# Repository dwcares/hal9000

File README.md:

# HAL9000 Voice Assistant

A voice assistant powered by OpenAI running on Particle microcontrollers. Press a button to talk, receive AI-generated spoken responses. Designed to fit inside the [Moebius Models 1:1 HAL9000 kit](https://www.amazon.com/Moebius-Models-HAL9000-Styrene-MOE20015/dp/B07SVCLLFW).

> "I'm sorry Dave, I'm afraid I can't do that."

## Overview

HAL9000 demonstrates bidirectional audio streaming between a Particle device (Photon/Argon) and a Node.js server. The server uses OpenAI's Whisper for speech-to-text, GPT for conversation, and TTS for speech synthesis.

## Hardware

A custom carrier PCB is available for clean assembly. See the [hardware folder](hardware/) for KiCad source files and manufacturing outputs.

### Components

| Component | Description | Connection |
|-----------|-------------|------------|
| Particle Photon | Wi-Fi MCU | Socket headers |
| MAX9814 Mic Module | Electret mic with AGC amp | J_MIC1 (3.3V/MIC/GND) |
| PAM8302A Amp Module | 2.5W Class-D mono amp | J_AMP1 (5V/AMP/GND) |
| 6mm Tactile Button | Push-to-talk | SW1 |
| 5mm LED | Status indicator | J_LED1 |
| Battery + Switch | Power input | J_BATT1, J_SW1 |
| Buck/Boost Converter | 5V regulated supply | J_BUCK1 |

### Quick Wiring (without PCB)

```
Particle Photon
┌─────────────────┐
│              A6 │──── Mic OUT (MAX9814)
│              A3 │──── Amp IN (PAM8302A)
│              D4 │──── Button ────┐
│             GND │────────────────┴── GND
│            3.3V │──── Mic VCC
│              5V │──── Amp VCC
│              D0 │──── LED+
└─────────────────┘
```

## Setup

### 1. Server Setup

```bash
cd server
npm install
```

Create a `.env` file:

```bash
cp .env.example .env
```

Edit `.env` with your credentials:

```
OPENAI_API_KEY=sk-your-key-here
PARTICLE_USERNAME=your-email@example.com
PARTICLE_PASSWORD=your-password
```

Start the server:

```bash
npm start
```

The server will:
- Login to Particle Cloud
- Publish its IP address for device discovery
- Listen for incoming device connections

### 2. Firmware Setup

Install the Particle CLI if you haven't:

```bash
npm install -g particle-cli
particle login
```

Install dependencies and flash:

```bash
cd firmware
particle library install
```

Compile and flash:

```bash
particle compile photon . --saveTo hal9000.bin
particle flash YOUR_DEVICE_NAME hal9000.bin
```

Or use Particle Workbench in VS Code.

> **Note:** No need to configure server IP - the device discovers it automatically via Particle Cloud!

## Usage

1. Power on the Particle device
2. Wait for the LED to indicate connection (solid on)
3. Press and hold the button to speak
4. Release the button when done
5. Wait for HAL's response through the speaker

## Configuration

### Server Options

| Environment Variable | Default | Description |
|---------------------|---------|-------------|
| `OPENAI_API_KEY` | - | Your OpenAI API key (required) |
| `PARTICLE_USERNAME` | - | Particle account email (for cloud discovery) |
| `PARTICLE_PASSWORD` | - | Particle account password |
| `PORT` | `5000` | Server port |
| `OPENAI_MODEL` | `gpt-4o` | Chat model |
| `OPENAI_VOICE` | `alloy` | TTS voice (alloy, echo, fable, onyx, nova, shimmer) |
| `SYSTEM_PROMPT` | (default) | AI personality prompt |
| `SAVE_RECORDINGS` | `false` | Save audio recordings to disk |

### Firmware Options

Edit the defines at the top of `hal9000.ino`:

```cpp
#define MIC_PIN      A6       // Microphone input
#define SPEAKER_PIN  A3       // Speaker output (DAC)
#define BUTTON_PIN   D4       // Push-to-talk button
#define LED_PIN      D0       // Status LED
#define SERVER_PORT  5000
```

## How Discovery Works

The server and device find each other automatically via Particle Cloud:

```
┌─────────────────┐                      ┌─────────────────┐
│  Node.js Server │                      │  Particle       │
│                 │                      │  Device         │
│ 1. Login to     │                      │                 │
│    Particle     │                      │ 3. Subscribe to │
│    Cloud        │                      │    server-ip    │
│                 │                      │    events       │
│ 2. Publish      │─── server-ip ───────►│                 │
│    server IP    │    (via cloud)       │ 4. Cache IP in  │
│                 │                      │    EEPROM       │
│ 5. Listen for   │◄── device-online ────│                 │
│    device-online│    (via cloud)       │ 5. Connect via  │
│    (republish)  │                      │    TCP          │
└─────────────────┘                      └─────────────────┘
```

- **First boot:** Device waits for server IP via cloud event
- **Subsequent boots:** Device uses cached IP for instant connect
- **Server restart:** Publishes new IP, devices update cache

## Dependencies

### Server
- [microstream-server](https://www.npmjs.com/package/microstream-server) - Audio streaming
- [particle-api-js](https://www.npmjs.com/package/particle-api-js) - Cloud discovery
- [openai](https://www.npmjs.com/package/openai) - AI services
- [dotenv](https://www.npmjs.com/package/dotenv) - Environment config

### Firmware
- [microstream](https://build.particle.io/libs/microstream) - Audio streaming library

## Troubleshooting

### No audio heard from speaker
- Check speaker wiring to DAC pin (A3 on Photon)
- Verify amplifier has power
- Check server console for "Playing response..." messages

### "Disconnected" status
- Verify server is running and reachable
- Check firewall allows port 5000
- Confirm device is on same network

### Transcription errors
- Speak clearly and close to microphone
- Check microphone wiring and amplifier gain
- Try adjusting `sampleRate` if audio quality is poor

## Architecture

```
┌─────────────────┐     TCP/WS      ┌─────────────────┐
│  Particle       │◄───────────────►│  Node.js        │
│  (microstream)  │                 │  (microstream-  │
│                 │                 │   server)       │
│  - Mic capture  │                 │                 │
│  - DAC playback │                 │  ┌───────────┐  │
│  - Button input │                 │  │ OpenAI    │  │
└─────────────────┘                 │  │ - Whisper │  │
                                    │  │ - GPT-4   │  │
                                    │  │ - TTS     │  │
                                    │  └───────────┘  │
                                    └─────────────────┘
```

## License

MIT License - see [LICENSE](LICENSE)

## Credits

Built with:
- [Microstream](https://github.com/dwcares/microstream) - Bidirectional audio streaming
- [OpenAI](https://openai.com) - AI services
- [Particle](https://particle.io) - IoT platform

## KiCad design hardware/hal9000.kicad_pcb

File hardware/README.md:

# HAL9000 Hardware

Custom carrier PCB for the HAL9000 voice assistant, designed in KiCad. This board is sized to mount inside the [Moebius Models 1:1 scale HAL9000 kit](https://www.amazon.com/Moebius-Models-HAL9000-Styrene-MOE20015/dp/B07SVCLLFW).

## Overview

This PCB provides a clean way to connect a Particle Photon to all the peripherals needed for the voice assistant:
- Microphone input with filtering
- Amplifier output for speaker
- Push-to-talk button
- Status LED
- Battery power with switch

## Files

| File | Description |
|------|-------------|
| `hal9000.kicad_pro` | KiCad project file |
| `hal9000.kicad_sch` | Schematic |
| `hal9000.kicad_pcb` | PCB layout |
| `hal9000_bom.csv` | Bill of materials |
| `manufacturing/` | Gerber files for fabrication |

## Bill of Materials

| Reference | Qty | Description | Notes |
|-----------|-----|-------------|-------|
| U1 | 1 | Particle Photon | Main MCU |
| J_PHOTON_L1, J_PHOTON_R1 | 2 | 12-pin Female Header 2.54mm | Photon sockets |
| J_BATT1 | 1 | 2-pin Header | Battery input (VBAT+, GND) |
| J_SW1 | 1 | 2-pin Header | Power switch |
| J_BUCK1 | 1 | 3-pin Header | Buck converter (VBAT+, GND, +5V) |
| J_MIC1 | 1 | 3-pin Header | Mic module (+3V3, MIC, GND) |
| J_AMP1 | 1 | 3-pin Header | Amp module (+5V, AMP, GND) |
| J_LED1 | 1 | 2-pin Header | LED (GND, LED+) |
| SW1 | 1 | 6mm Tactile Button | Push-to-talk |
| R1 | 1 | 220Ω 0805 | LED current limiter |
| R2 | 1 | 1kΩ 0805 | Mic input filter |
| C1 | 1 | 10nF 0805 | Mic input filter |
| C2 | 1 | 470µF Electrolytic | 5V bulk capacitance |

## External Modules

These modules connect via headers:

| Module | Description | Header |
|--------|-------------|--------|
| MAX9814 | Electret mic with AGC amplifier | J_MIC1 |
| PAM8302A | 2.5W Class-D mono amplifier | J_AMP1 |
| Buck/Boost Converter | 5V regulated output | J_BUCK1 |

## Pin Mapping

| Signal | Photon Pin | Description |
|--------|------------|-------------|
| MIC | A6 | Microphone analog input |
| AMP | A3 (DAC) | Speaker DAC output |
| BUTTON | D4 | Push-to-talk input |
| LED | D0 | Status LED output |

## Power

The board supports battery power with an external switch:

```
Battery ──► J_BATT1 ──► J_SW1 (switch) ──► Buck Converter ──► J_BUCK1 (+5V out)
                                                                    │
                                                              Photon VIN
                                                                    │
                                                              Onboard 3.3V reg
```

- **5V rail**: Powers Photon (via VIN), amplifier module
- **3.3V rail**: Powers microphone module (from Photon regulator)

## Manufacturing

The `manufacturing/` folder contains Gerber files ready for PCB fabrication. Upload to your preferred PCB manufacturer (JLCPCB, PCBWay, OSH Park, etc.).

## Assembly Tips

1. Solder SMD components first (R1, R2, C1)
2. Install female headers for Photon (J_PHOTON_L1, J_PHOTON_R1)
3. Install remaining through-hole headers and button
4. Add electrolytic capacitor C2 (observe polarity)
5. Connect external modules via headers
6. Insert Particle Photon

## License

MIT License - see [LICENSE](../LICENSE)

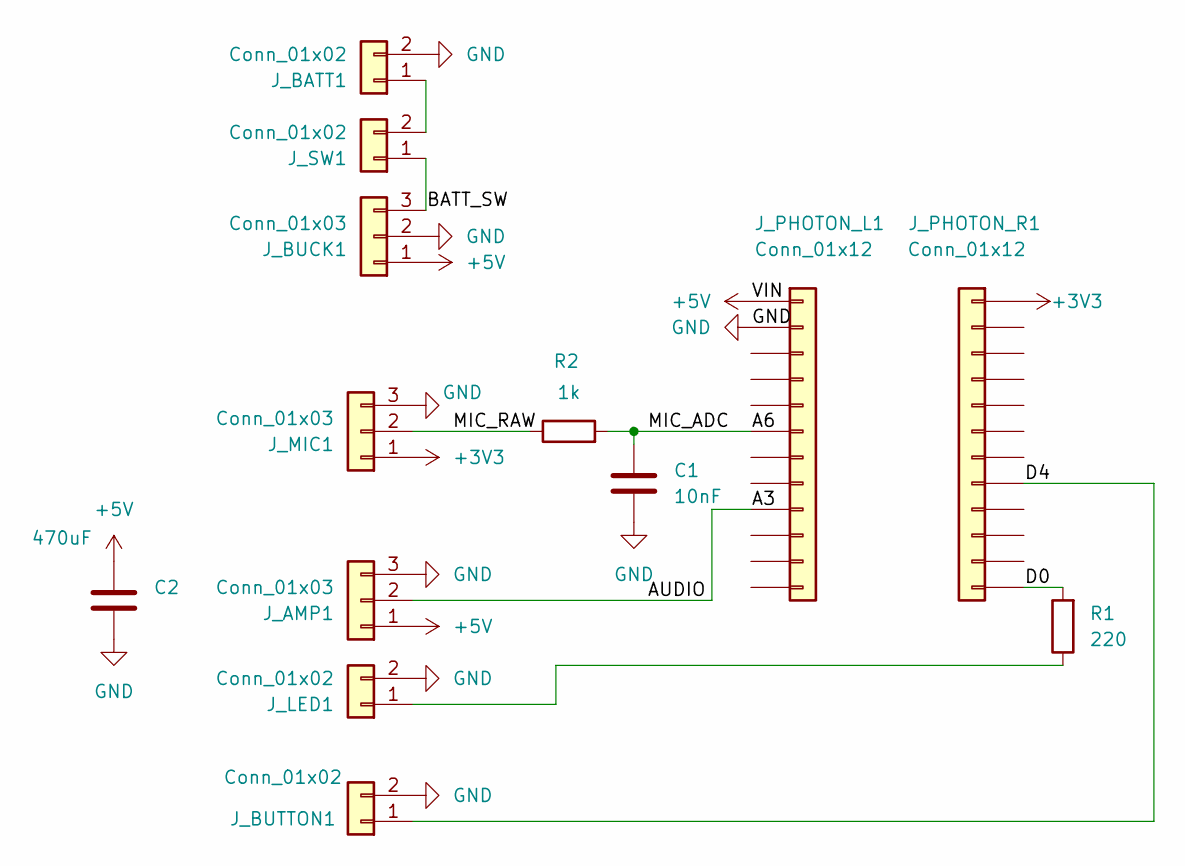
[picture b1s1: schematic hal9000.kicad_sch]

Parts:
C1: 10nF; C_0805_2012Metric_Pad1.18x1.45mm_HandSolder
C2: 470uF; CP_Radial_D6.3mm_P2.50mm
J_AMP1: Conn_01x03; PinHeader_1x03_P2.54mm_Vertical
J_BATT1: Conn_01x02; PinHeader_1x02_P2.54mm_Vertical
J_BUCK1: Conn_01x03; PinHeader_1x03_P2.54mm_Vertical
J_BUTTON1: Conn_01x02; PinHeader_1x02_P2.54mm_Vertical
J_LED1: Conn_01x02; PinHeader_1x02_P2.54mm_Vertical
J_MIC1: Conn_01x03; PinHeader_1x03_P2.54mm_Vertical
J_PHOTON_L1: Conn_01x12; PinSocket_1x12_P2.54mm_Vertical
J_PHOTON_R1: Conn_01x12; PinSocket_1x12_P2.54mm_Vertical
J_SW1: Conn_01x02; PinHeader_1x02_P2.54mm_Vertical
R1: 220; R_0805_2012Metric_Pad1.20x1.40mm_HandSolder
R2: 1k; R_0805_2012Metric_Pad1.20x1.40mm_HandSolder

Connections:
+3V3: J_MIC1.1, J_PHOTON_R1.1
+5V: C2.1, J_AMP1.1, J_BUCK1.1, J_PHOTON_L1.1
/A3: J_AMP1.2, J_PHOTON_L1.9
/A6: C1.2, J_PHOTON_L1.6, R2.2
/BATT_SW: J_BUCK1.3, J_SW1.1
/D0: J_PHOTON_R1.12, R1.2
/D4: J_BUTTON1.1, J_PHOTON_R1.8
/MIC_RAW: J_MIC1.2, R2.1
GND: C1.1, C2.2, J_AMP1.3, J_BATT1.2, J_BUCK1.2, J_BUTTON1.2, J_LED1.2, J_MIC1.3, J_PHOTON_L1.2
unnamed: J_BATT1.1, J_SW1.2
unnamed: J_LED1.1, R1.1

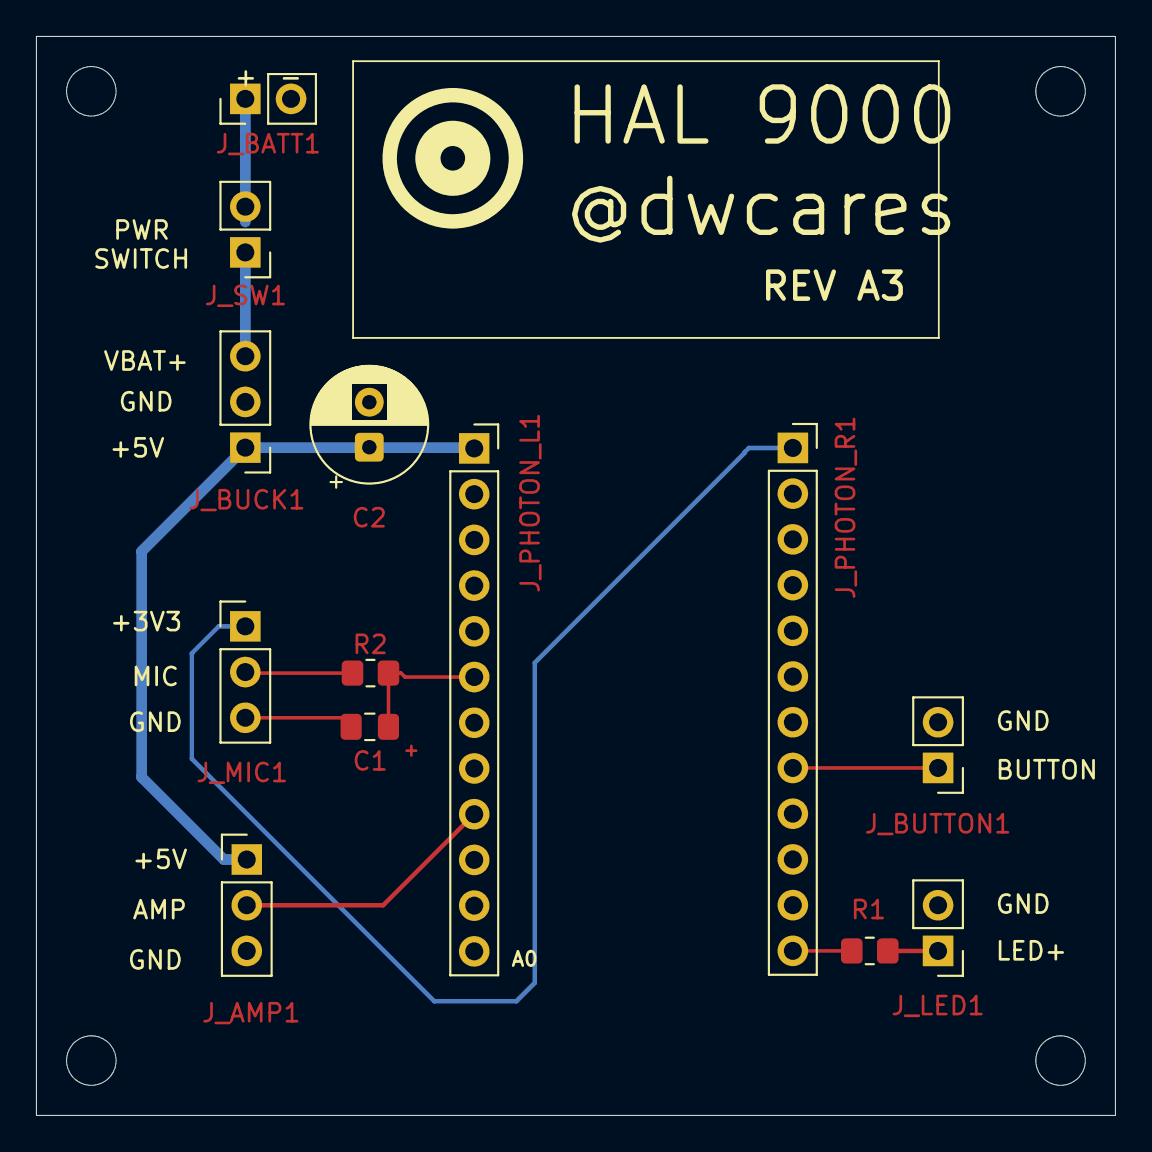
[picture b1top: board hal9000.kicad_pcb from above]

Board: 2 copper layers, 59.9 x 59.9 mm, 13 parts (0 on the bottom side), 11 nets.

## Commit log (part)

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2026-03-27 hw: reva2 kicad files
2026-04-01 Update hw/fw to match reva2 and reva3 pushbutton at D4
